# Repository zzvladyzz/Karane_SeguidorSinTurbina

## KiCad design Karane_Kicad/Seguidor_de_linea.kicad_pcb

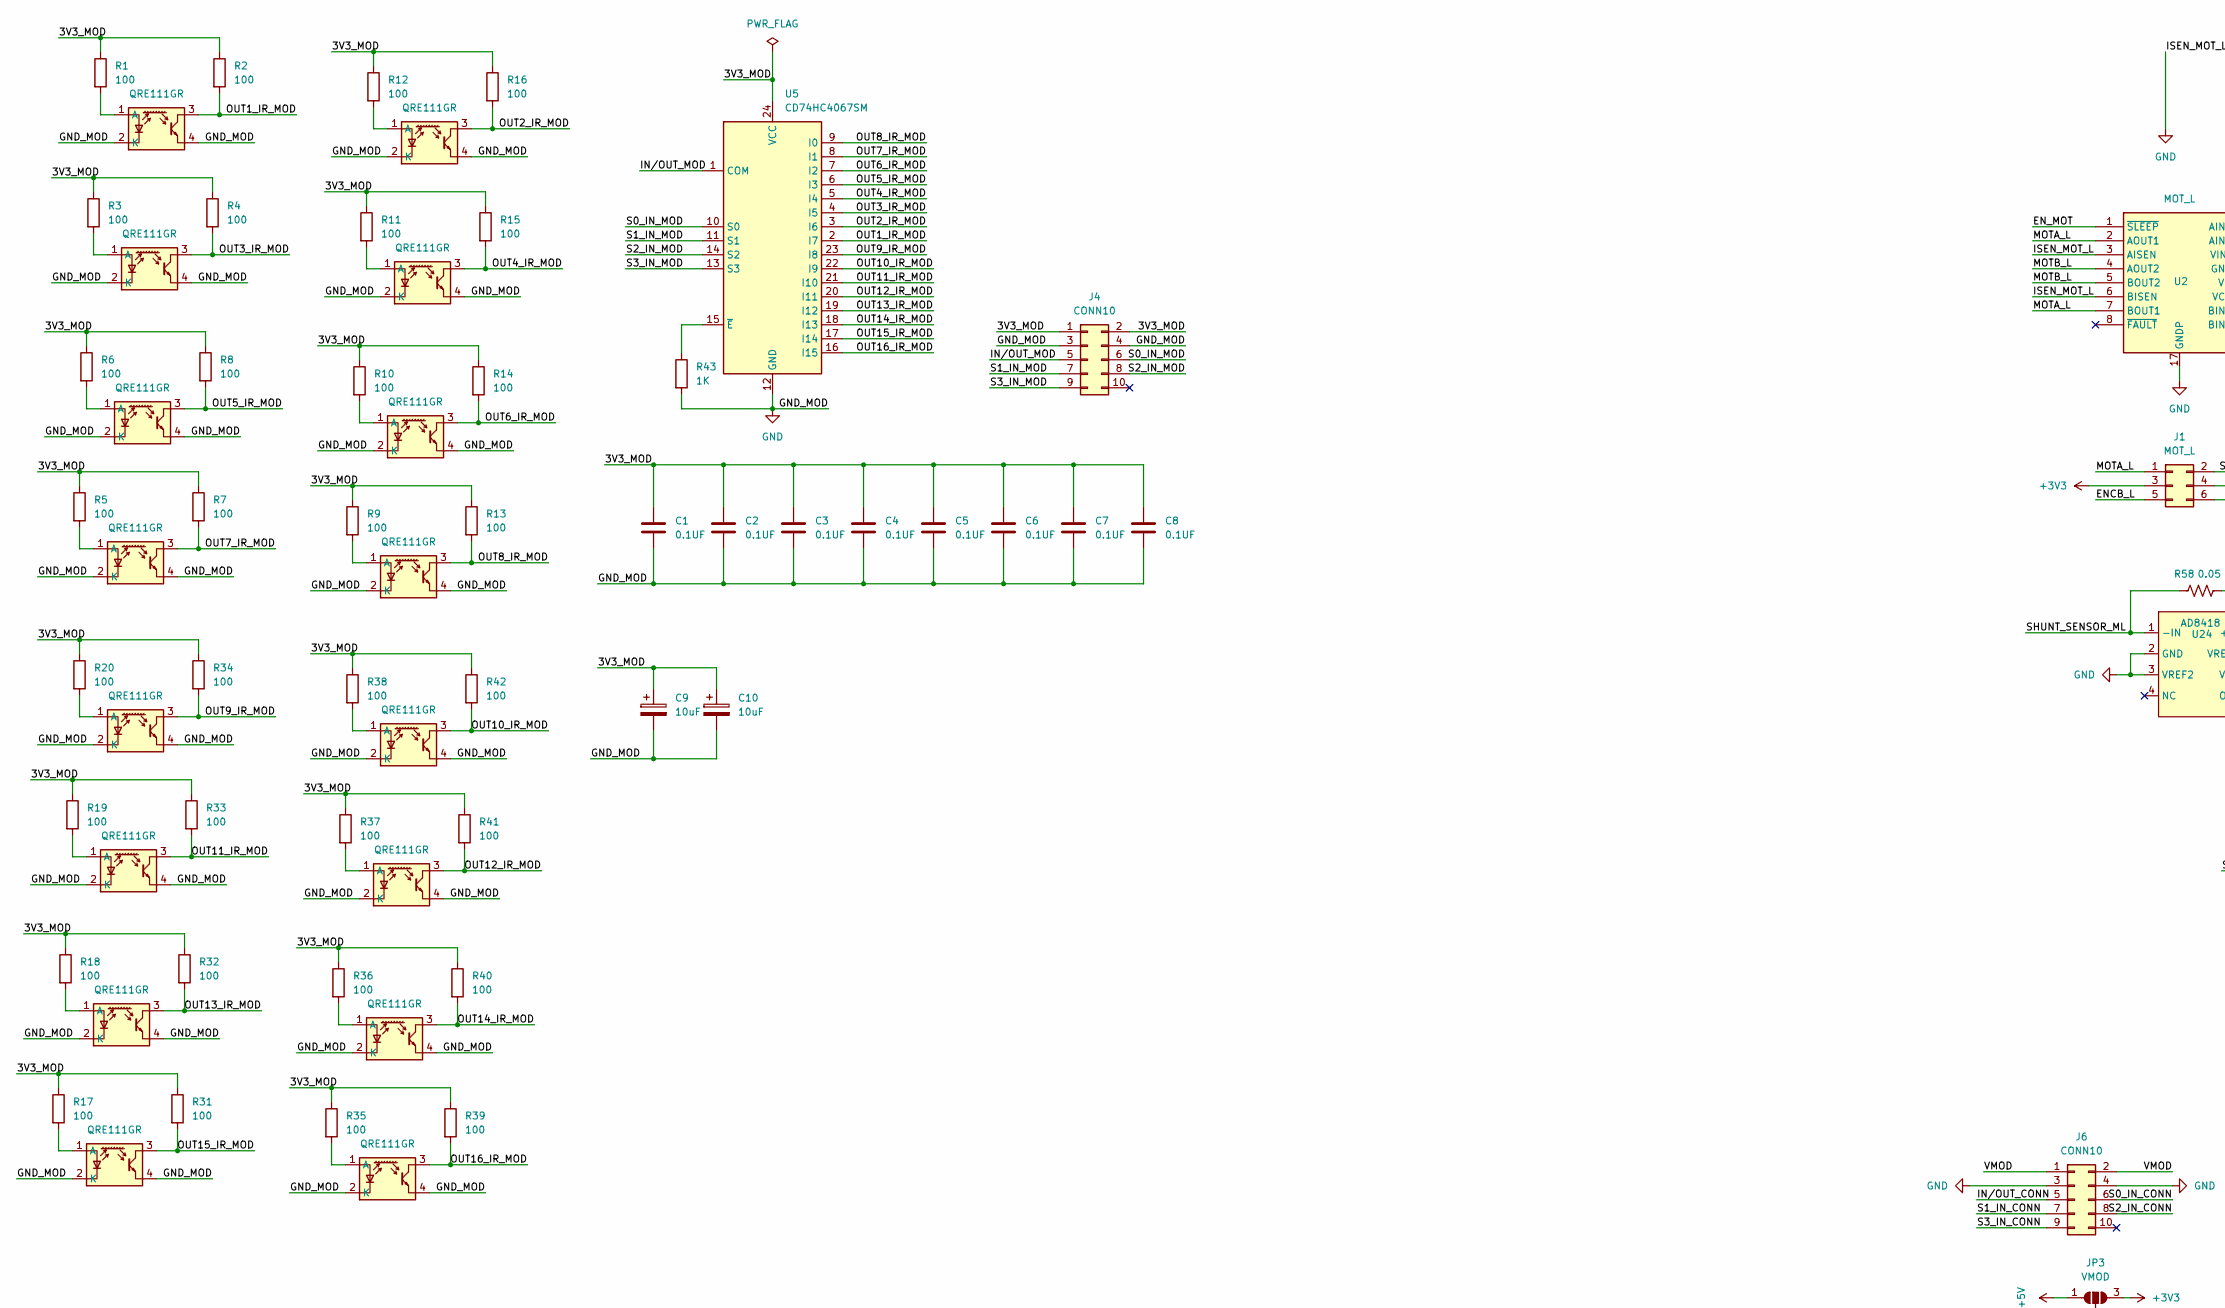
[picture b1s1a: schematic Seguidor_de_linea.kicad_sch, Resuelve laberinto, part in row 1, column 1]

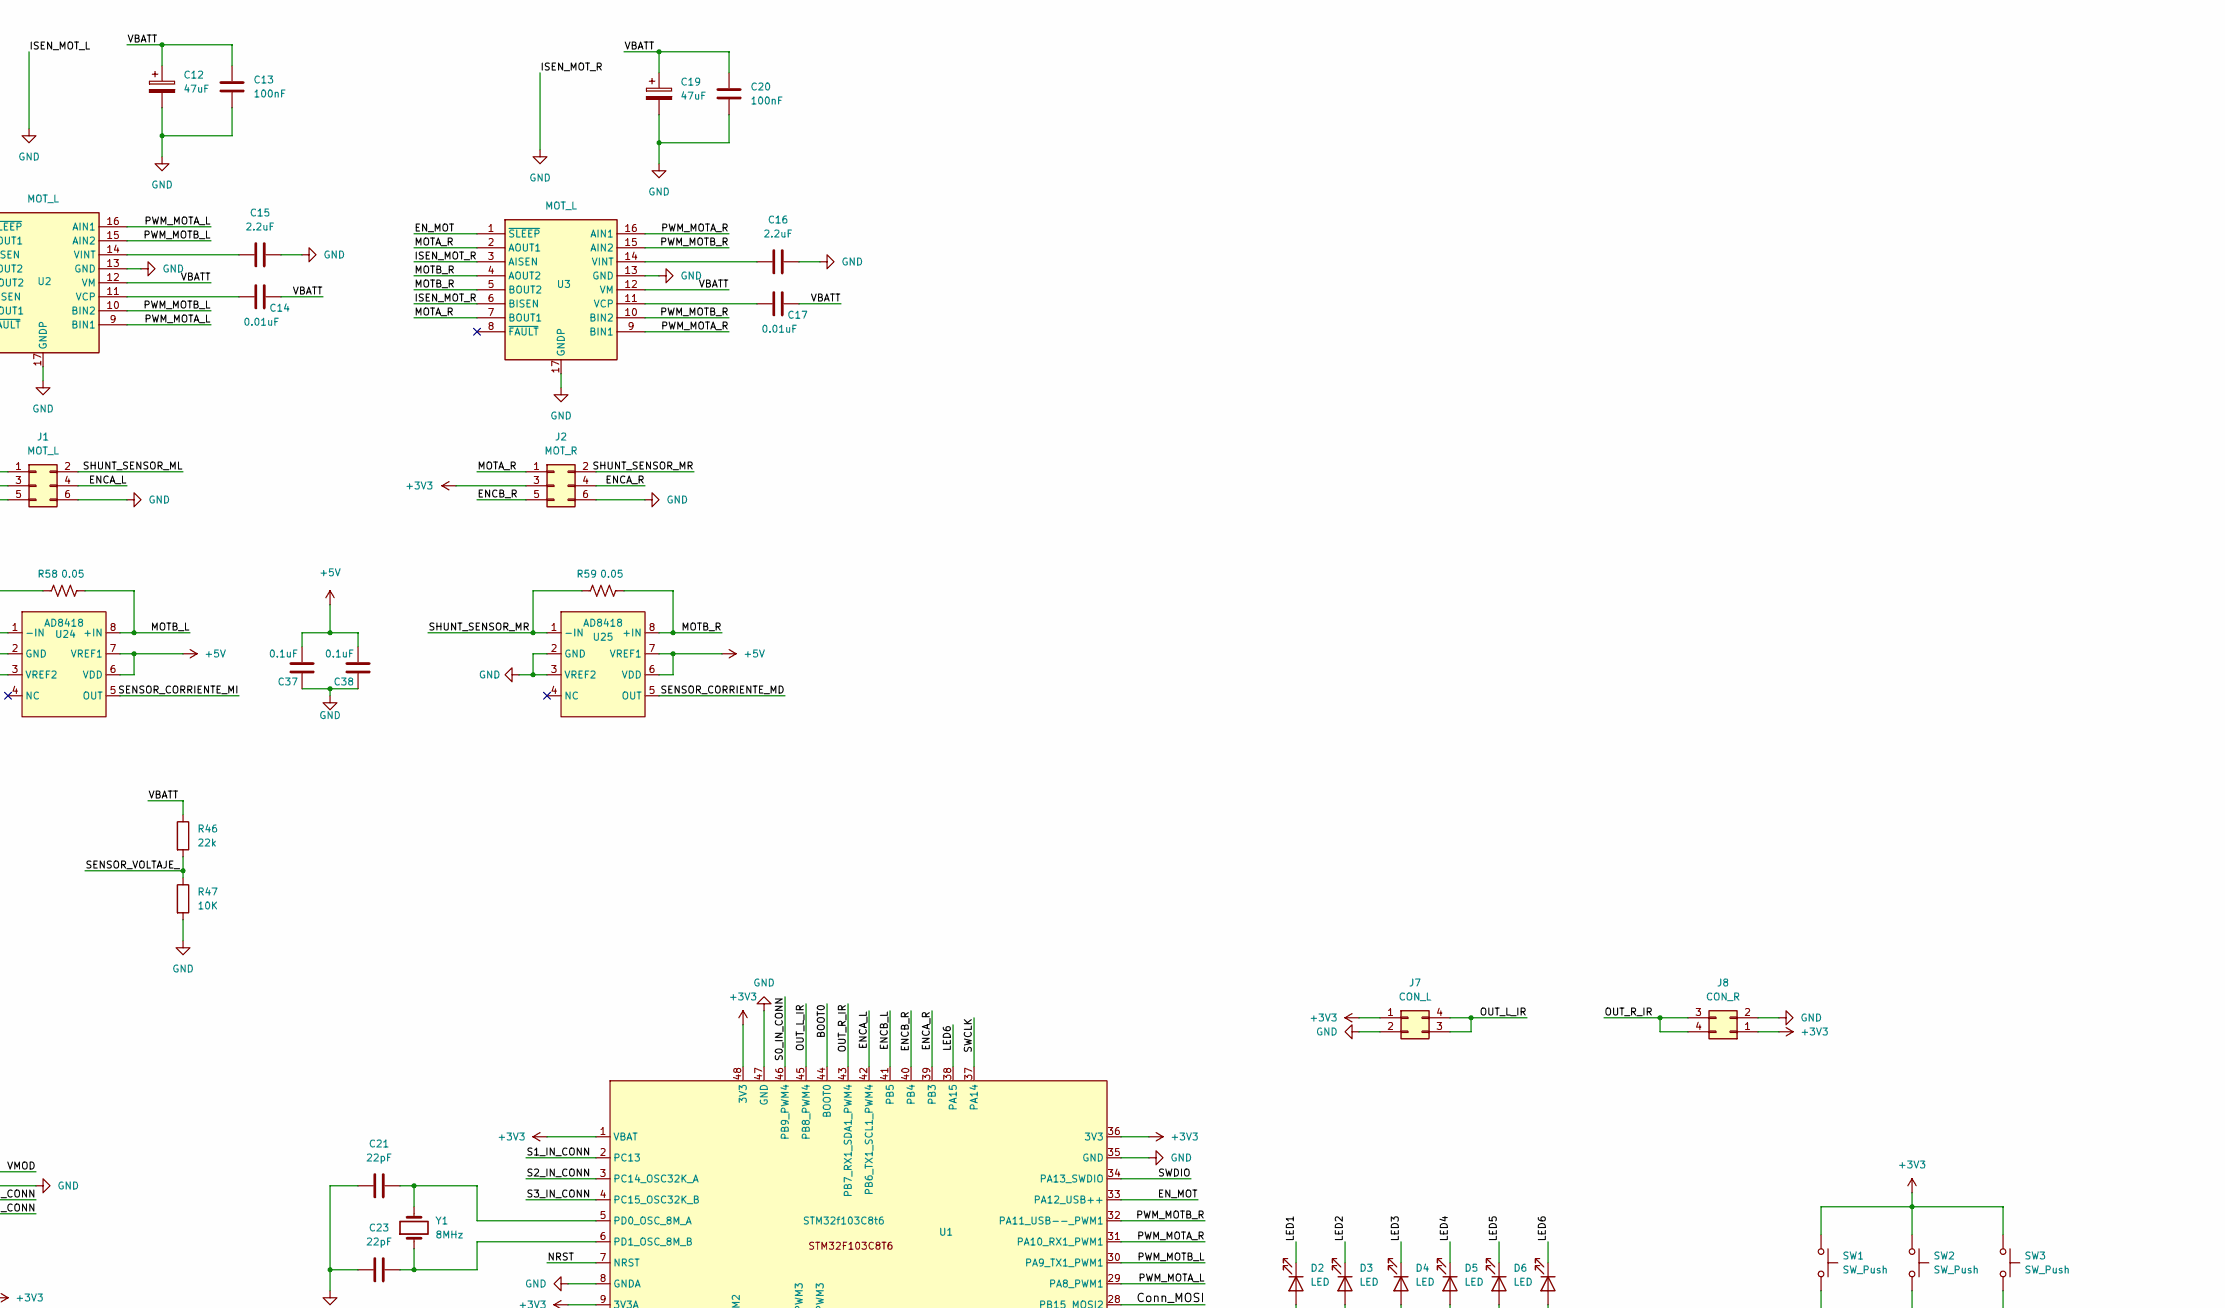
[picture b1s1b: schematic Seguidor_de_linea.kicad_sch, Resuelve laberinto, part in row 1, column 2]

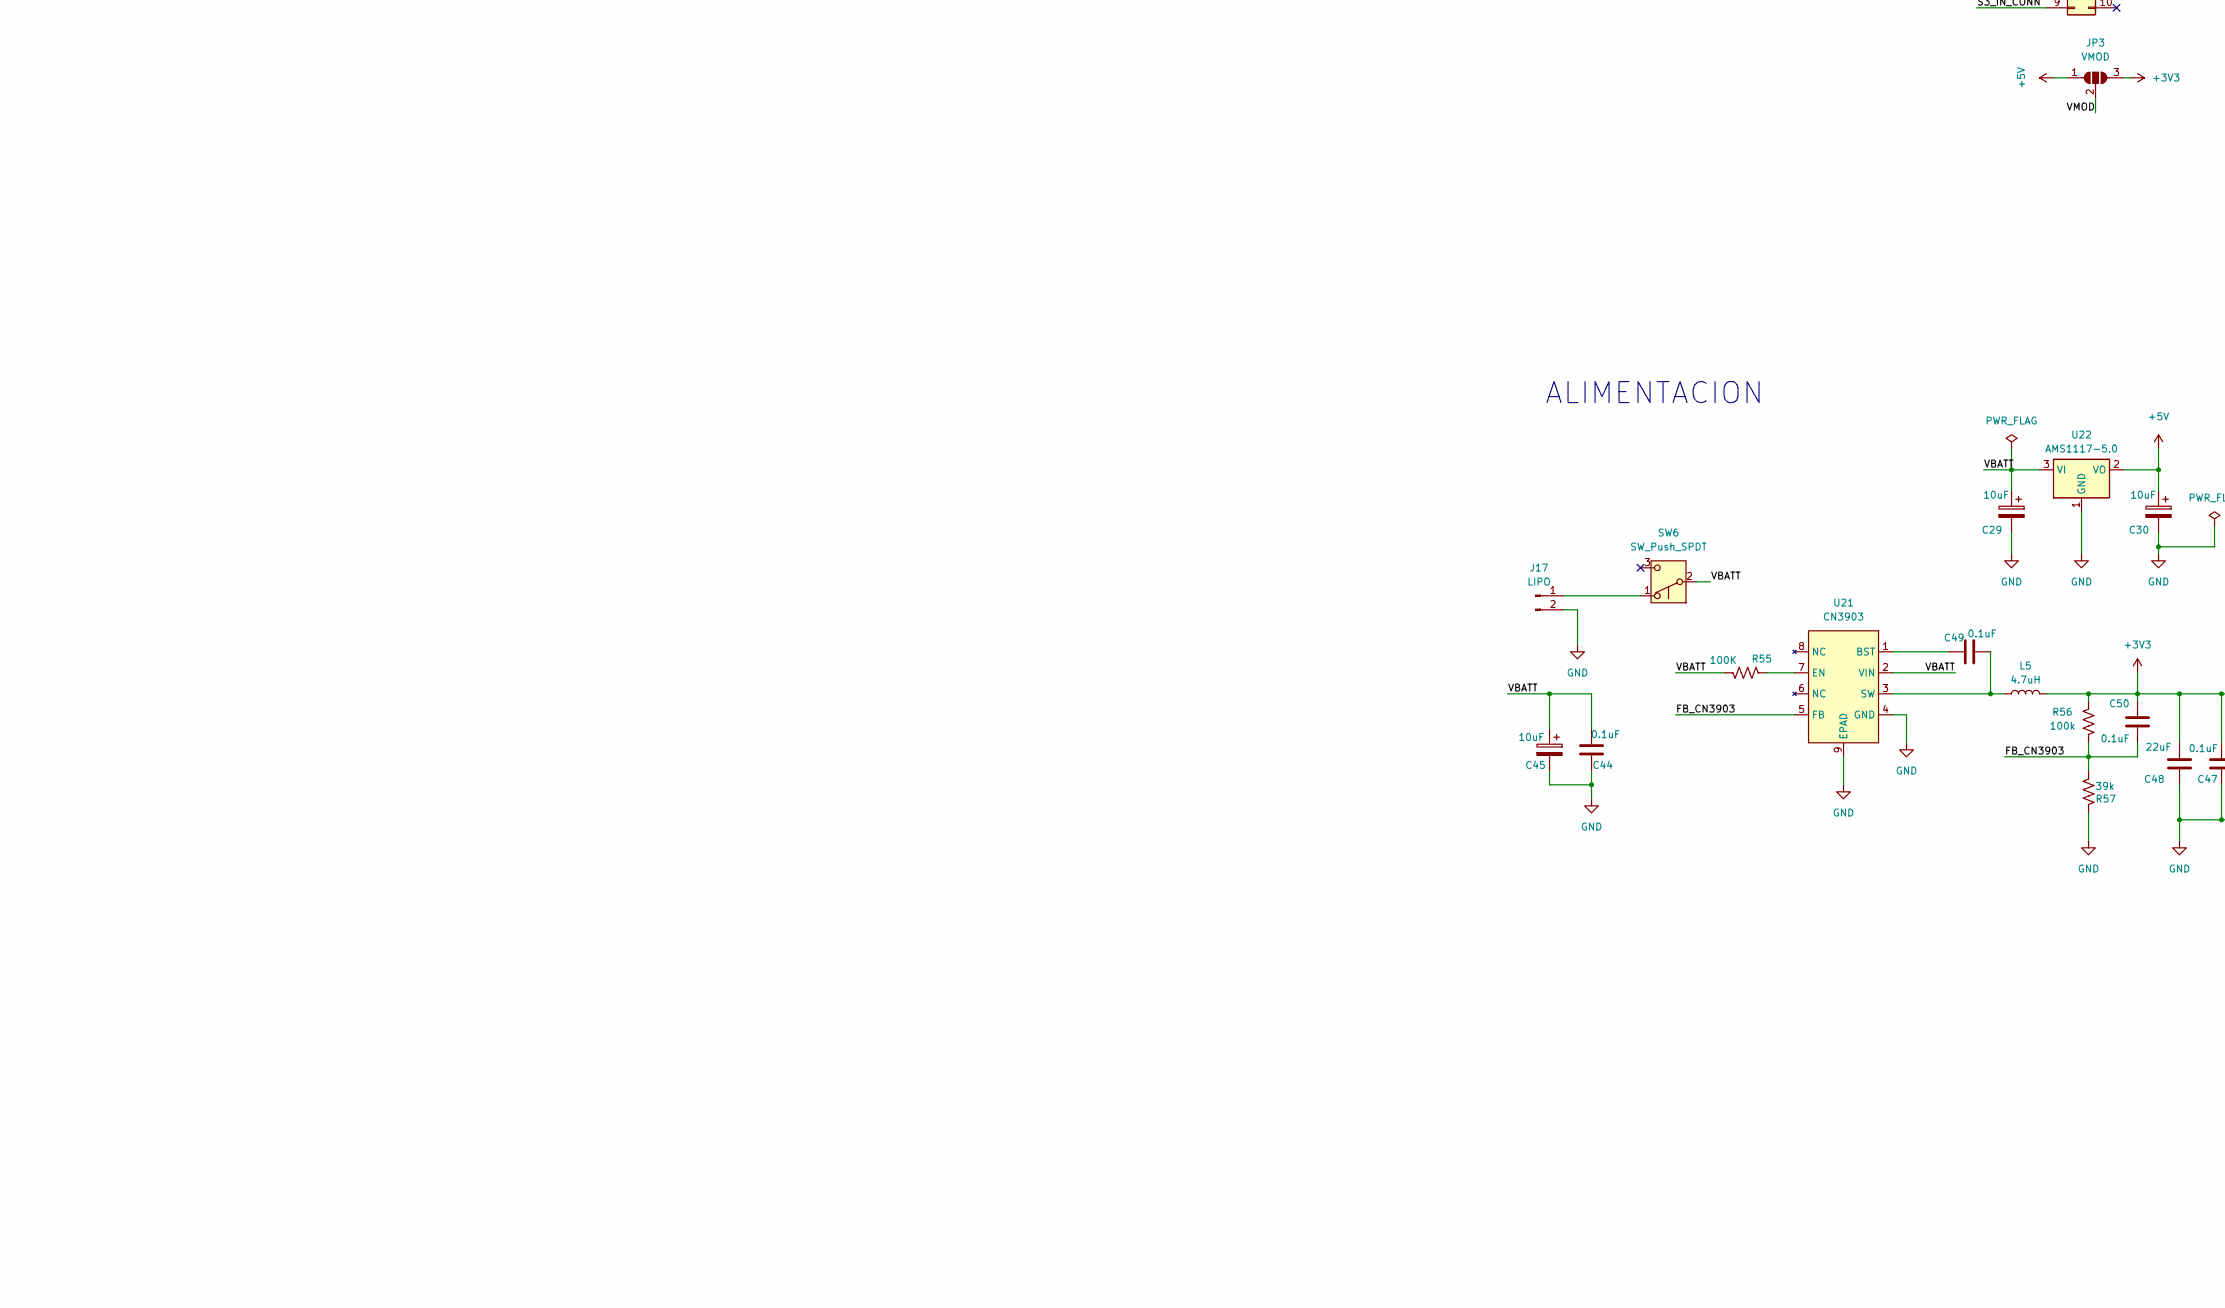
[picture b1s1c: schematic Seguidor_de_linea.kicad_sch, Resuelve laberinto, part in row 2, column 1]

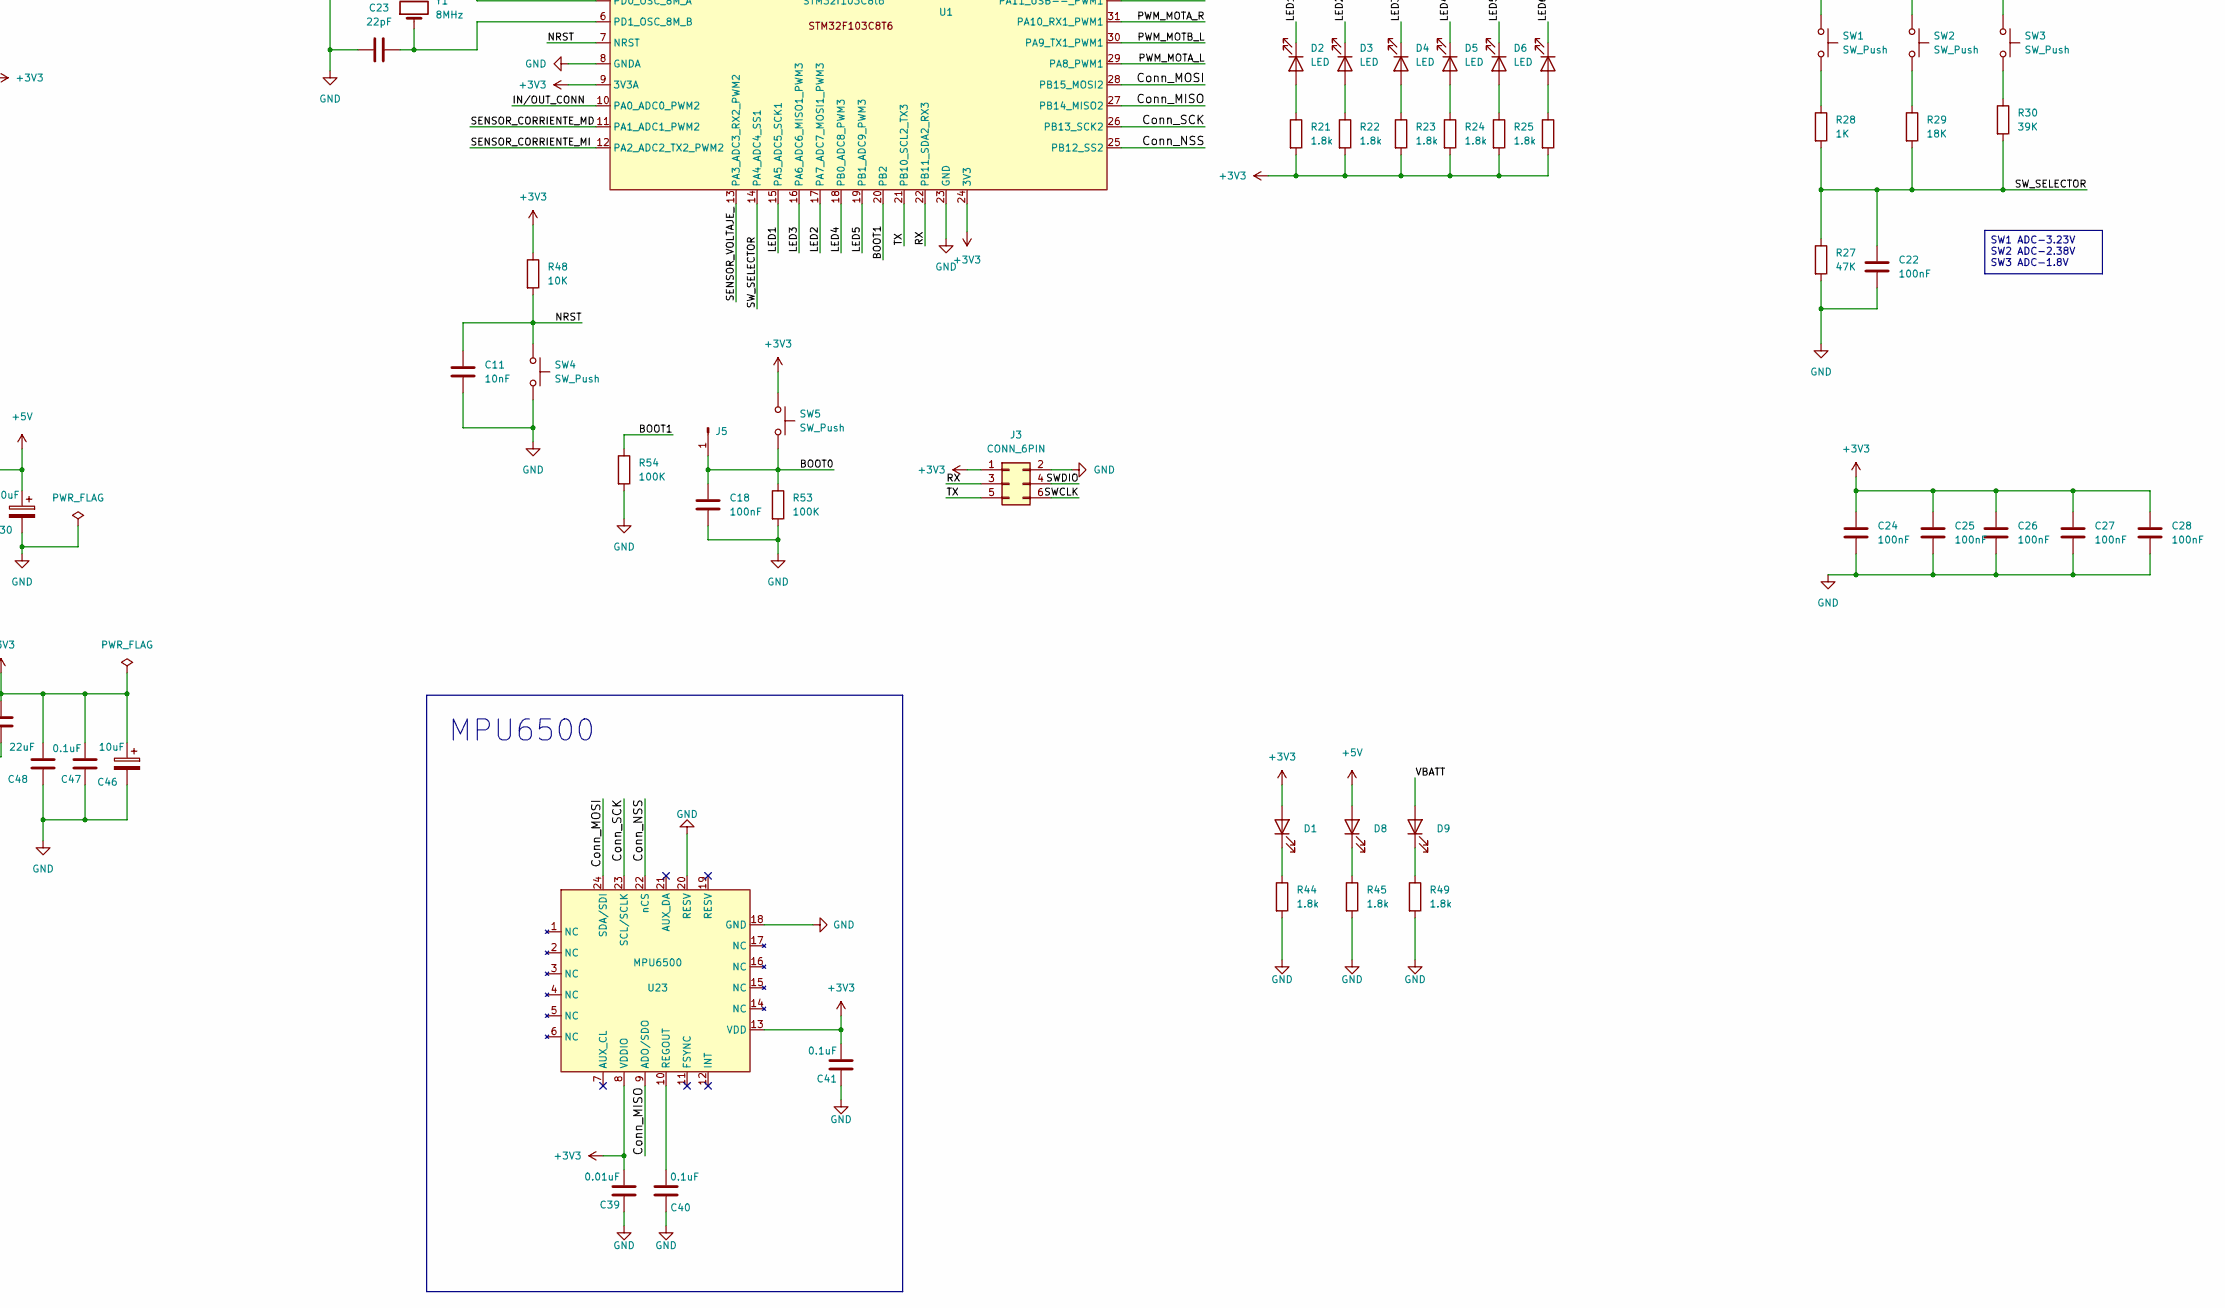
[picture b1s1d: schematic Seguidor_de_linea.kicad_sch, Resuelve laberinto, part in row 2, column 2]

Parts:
C1, C2, C3, C4, C5, C6, C7, C8: 0.1UF; C_1206_3216Metric_Pad1.33x1.80mm_HandSolder
C9, C10: 10uF; CP_EIA-6032-15_Kemet-U_HandSolder
C11: 10nF; C_1206_3216Metric_Pad1.33x1.80mm_HandSolder
C12, C19: 47uF; C_1210_3225Metric_Pad1.33x2.70mm_HandSolder
C13, C18, C20, C22, C24, C25, C26, C27, C28: 100nF; C_1206_3216Metric_Pad1.33x1.80mm_HandSolder
C14, C17: 0.01uF; C_1206_3216Metric_Pad1.33x1.80mm_HandSolder
C15, C16: 2.2uF; C_1206_3216Metric_Pad1.33x1.80mm_HandSolder
C21, C23: 22pF; C_0805_2012Metric_Pad1.18x1.45mm_HandSolder
C29, C45, C46: 10uF; CP_Elec_4x5.4
C30: 10uF; C_1206_3216Metric_Pad1.33x1.80mm_HandSolder
C37, C38, C44, C47, C49, C50: 0.1uF; C_1206_3216Metric_Pad1.33x1.80mm_HandSolder
C39: 0.01uF; C_0805_2012Metric_Pad1.18x1.45mm_HandSolder
C40, C41: 0.1uF; C_0805_2012Metric_Pad1.18x1.45mm_HandSolder
C48: 22uF; C_1206_3216Metric_Pad1.33x1.80mm_HandSolder
D1, D2, D3, D4, D5, D6, D7, D8, D9: LED; LED_1206_3216Metric
J1: MOT_L; IDC-Header_2x03_P2.54mm_Vertical
J2: MOT_R; IDC-Header_2x03_P2.54mm_Vertical
J3: CONN_6PIN; IDC-Header_2x03_P2.54mm_Vertical
J4, J6: CONN10; IDC-Header_2x05_P2.54mm_Vertical
J5: NRST; PinHeader_1x01_P2.54mm_Vertical
J7: CON_L; PinHeader_2x02_P2.54mm_Vertical
J8: CON_R; PinHeader_2x02_P2.54mm_Vertical
J17: LIPO; PinHeader_1x02_P2.54mm_Vertical
JP3: VMOD; SolderJumper-3_P1.3mm_Open_Pad1.0x1.5mm_NumberLabels
L5: 4.7uH; L_Wuerth_HCM-7050
R1, R2, R3, R4, R5, R6, R7, R8, R9, R10, R11, R12, R13, R14, R15, R16, R17, R18, R19, R20, R31, R32, R33, R34, R35, R36, R37, R38, R39, R40, R41, R42: 100; R_1206_3216Metric_Pad1.30x1.75mm_HandSolder
R21, R22, R23, R24, R25, R26, R44, R45, R49: 1.8k; R_1206_3216Metric
R27: 47K; R_1206_3216Metric
R28, R43: 1K; R_1206_3216Metric
R29: 18K; R_1206_3216Metric
R30: 39K; R_1206_3216Metric
R46: 22k; R_1206_3216Metric
R47, R48: 10K; R_1206_3216Metric
R53, R54: 100K; R_1206_3216Metric
R55: 100K; R_0805_2012Metric_Pad1.20x1.40mm_HandSolder
R56: 100k; R_0805_2012Metric_Pad1.20x1.40mm_HandSolder
R57: 39k; R_0805_2012Metric_Pad1.20x1.40mm_HandSolder
R58, R59: 0.05; R_2512_6332Metric_Pad1.40x3.35mm_HandSolder
SW1, SW2, SW3, SW4, SW5: SW_Push; SW_SPST_CK_RS282G05A3
SW6: SW_Push_SPDT; SW_SPDT_PCM12
U1: STM32f103C8t6; LQFP-48_7x7mm_P0.5mm
U2, U3: MOT_L; HTSSOP-16-1EP_4.4x5mm_P0.65mm_EP3.4x5mm_Mask2.46x2.31mm_The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
U4, U6, U7, U8, U9, U10, U11, U12, U13, U14, U15, U16, U17, U18, U19, U20: QRE111GR; QRE1113GR_IR
U5: CD74HC4067SM; SSOP-24_5.3x8.2mm_P0.65mm
U21: CN3903; SOP-8-1EP_4.57x4.57mm_P1.27mm_EP4.57x4.45mm
U22: AMS1117-5.0; SOT-223-3_TabPin2
U23: MPU6500; InvenSense_QFN-24_3x3mm_P0.4mm
U24, U25: AD8418
Y1: 8MHz; Crystal_HC49-U_Vertical

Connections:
+3V3: C24.1, C25.1, C26.1, C27.1, C28.1, C39.2, C41.2, C46.1, C47.1, C48.1, C50.2, D1.2 (A), J1.3, J2.3, J3.1, J7.1, J8.1, JP3.3 (B), L5.1, R21.2, R22.2, R23.2, R24.2, R25.2, R26.2, R48.1, R56.1, SW1.1, SW2.1, SW3.1, SW5.1, U1.1 (VBAT), U1.9 (3V3A), U1.24 (3V3), U1.36 (3V3), U1.48 (3V3), U23.8 (VDDIO), U23.13 (VDD)
+5V: C30.1, C37.2, C38.2, D8.2 (A), JP3.1 (A), U22.2 (VO), U24.6 (VDD), U24.7 (VREF1), U25.6 (VDD), U25.7 (VREF1)
/3V3_MOD: C1.1, C2.1, C3.1, C4.1, C5.1, C6.1, C7.1, C8.1, C9.1, C10.1, J4.1, J4.2, R1.1, R2.1, R3.1, R4.1, R5.1, R6.1, R7.1, R8.1, R9.1, R10.1, R11.1, R12.1, R13.1, R14.1, R15.1, R16.1, R17.1, R18.1, R19.1, R20.1, R31.1, R32.1, R33.1, R34.1, R35.1, R36.1, R37.1, R38.1, R39.1, R40.1, R41.1, R42.1, U5.24 (VCC)
/BOOT0: C18.1, J5.1, R53.1, SW5.2, U1.44 (BOOT0)
/BOOT1: R54.1, U1.20 (PB2)
/Conn_MISO: U1.27 (PB14_MISO2), U23.9 (ADO/SDO)
/Conn_MOSI: U1.28 (PB15_MOSI2), U23.24 (SDA/SDI)
/Conn_NSS: U1.25 (PB12_SS2), U23.22 (nCS)
/Conn_SCK: U1.26 (PB13_SCK2), U23.23 (SCL/SCLK)
/ENCA_L: J1.4, U1.42 (PB6_TX1_SCL1_PWM4)
/ENCA_R: J2.4, U1.39 (PB3)
/ENCB_L: J1.5, U1.41 (PB5)
/ENCB_R: J2.5, U1.40 (PB4)
/EN_MOT: U1.33 (PA12_USB++), U2.1 (~SLEEP), U3.1 (~SLEEP)
/FB_CN3903: C50.1, R56.2, R57.1, U21.5 (FB)
/IN/OUT_CONN: J6.5, U1.10 (PA0_ADC0_PWM2)
/IN/OUT_MOD: J4.5, U5.1 (COM)
/LED1: D2.1 (K), U1.15 (PA5_ADC5_SCK1)
/LED2: D3.1 (K), U1.17 (PA7_ADC7_MOSI1_PWM3)
/LED3: D4.1 (K), U1.16 (PA6_ADC6_MISO1_PWM3)
/LED4: D5.1 (K), U1.18 (PB0_ADC8_PWM3)
/LED5: D6.1 (K), U1.19 (PB1_ADC9_PWM3)
/LED6: D7.1 (K), U1.38 (PA15)
/MOTA_L: J1.1, U2.2 (AOUT1), U2.7 (BOUT1)
/MOTA_R: J2.1, U3.2 (AOUT1), U3.7 (BOUT1)
/MOTB_L: R58.2, U2.4 (AOUT2), U2.5 (BOUT2), U24.8 (+IN)
/MOTB_R: R59.2, U3.4 (AOUT2), U3.5 (BOUT2), U25.8 (+IN)
/NRST: C11.1, R48.2, SW4.1, U1.7 (NRST)
/OUT1_IR_MOD: R2.2, U4.3, U5.2 (I7)
/OUT2_IR_MOD: R16.2, U5.3 (I6), U12.3
/OUT3_IR_MOD: R4.2, U5.4 (I5), U6.3
/OUT4_IR_MOD: R15.2, U5.5 (I4), U11.3
/OUT5_IR_MOD: R8.2, U5.6 (I3), U8.3
/OUT6_IR_MOD: R14.2, U5.7 (I2), U10.3
/OUT7_IR_MOD: R7.2, U5.8 (I1), U7.3
/OUT8_IR_MOD: R13.2, U5.9 (I0), U9.3
/OUT9_IR_MOD: R34.2, U5.23 (I8), U16.3
/OUT10_IR_MOD: R42.2, U5.22 (I9), U20.3
/OUT11_IR_MOD: R33.2, U5.21 (I10), U15.3
/OUT12_IR_MOD: R41.2, U5.20 (I11), U19.3
/OUT13_IR_MOD: R32.2, U5.19 (I12), U14.3
/OUT14_IR_MOD: R40.2, U5.18 (I13), U18.3
/OUT15_IR_MOD: R31.2, U5.17 (I14), U13.3
/OUT16_IR_MOD: R39.2, U5.16 (I15), U17.3
/OUT_L_IR: J7.3, J7.4, U1.45 (PB8_PWM4)
/OUT_R_IR: J8.3, J8.4, U1.43 (PB7_RX1_SDA1_PWM4)
/PWM_MOTA_L: U1.29 (PA8_PWM1), U2.9 (BIN1), U2.16 (AIN1)
/PWM_MOTA_R: U1.31 (PA10_RX1_PWM1), U3.9 (BIN1), U3.16 (AIN1)
/PWM_MOTB_L: U1.30 (PA9_TX1_PWM1), U2.10 (BIN2), U2.15 (AIN2)
/PWM_MOTB_R: U1.32 (PA11_USB--_PWM1), U3.10 (BIN2), U3.15 (AIN2)
/RX: J3.3, U1.22 (PB11_SDA2_RX3)
/S0_IN_CONN: J6.6, U1.46 (PB9_PWM4)
/S0_IN_MOD: J4.6, U5.10 (S0)
/S1_IN_CONN: J6.7, U1.2 (PC13)
/S1_IN_MOD: J4.7, U5.11 (S1)
/S2_IN_CONN: J6.8, U1.3 (PC14_OSC32K_A)
/S2_IN_MOD: J4.8, U5.14 (S2)
/S3_IN_CONN: J6.9, U1.4 (PC15_OSC32K_B)
/S3_IN_MOD: J4.9, U5.13 (S3)
/SENSOR_CORRIENTE_MD: U1.11 (PA1_ADC1_PWM2), U25.5 (OUT)
/SENSOR_CORRIENTE_MI: U1.12 (PA2_ADC2_TX2_PWM2), U24.5 (OUT)
/SENSOR_VOLTAJE_: R46.2, R47.1, U1.13 (PA3_ADC3_RX2_PWM2)
/SHUNT_SENSOR_ML: J1.2, R58.1, U24.1 (-IN)
/SHUNT_SENSOR_MR: J2.2, R59.1, U25.1 (-IN)
/SWCLK: J3.6, U1.37 (PA14)
/SWDIO: J3.4, U1.34 (PA13_SWDIO)
/SW_SELECTOR: C22.1, R27.1, R28.2, R29.2, R30.2, U1.14 (PA4_ADC4_SS1)
/TX: J3.5, U1.21 (PB10_SCL2_TX3)
/VBATT: C12.1, C13.1, C14.2, C17.2, C19.1, C20.1, C29.1, C44.1, C45.1, D9.2 (A), R46.1, R55.2, SW6.2 (B), U2.12 (VM), U3.12 (VM), U21.2 (VIN), U22.3 (VI)
/VMOD: J6.1, J6.2, JP3.2 (C)
GND: C1.2, C2.2, C3.2, C4.2, C5.2, C6.2, C7.2, C8.2, C9.2, C10.2, C11.2, C12.2, C13.2, C15.2, C16.2, C18.2, C19.2, C20.2, C21.1, C22.2, C23.2, C24.2, C25.2, C26.2, C27.2, C28.2, C29.2, C30.2, C37.1, C38.1, C39.1, C40.1, C41.1, C44.2, C45.2, C46.2, C47.2, C48.2, J1.6, J2.6, J3.2, J4.3, J4.4, J6.3, J6.4, J7.2, J8.2, J17.2, R27.2, R43.2, R44.2, R45.2, R47.2, R49.2, R53.2, R54.2, R57.2, SW4.2, U1.8 (GNDA), U1.23 (GND), U1.35 (GND), U1.47 (GND), U2.3 (AISEN), U2.6 (BISEN), U2.13 (GND), U2.17 (GNDP), U3.3 (AISEN), U3.6 (BISEN), U3.13 (GND), U3.17 (GNDP), U4.2 (K), U4.4, U5.12 (GND), U6.2 (K), U6.4, U7.2 (K), U7.4, U8.2 (K), U8.4, U9.2 (K), U9.4, U10.2 (K), U10.4, U11.2 (K), U11.4, U12.2 (K), U12.4, U13.2 (K), U13.4, U14.2 (K), U14.4, U15.2 (K), U15.4, U16.2 (K), U16.4, U17.2 (K), U17.4, U18.2 (K), U18.4, U19.2 (K), U19.4, U20.2 (K), U20.4, U21.4 (GND), U21.9 (EPAD), U22.1 (GND), U23.18 (GND), U23.20 (RESV), U24.2 (GND), U24.3 (VREF2), U25.2 (GND), U25.3 (VREF2)
unnamed: D1.1 (K), R44.1
unnamed: D2.2 (A), R21.1
unnamed: D3.2 (A), R22.1
unnamed: D4.2 (A), R23.1
unnamed: D5.2 (A), R24.1
unnamed: D6.2 (A), R25.1
unnamed: D7.2 (A), R26.1
unnamed: D8.1 (K), R45.1
unnamed: D9.1 (K), R49.1
unnamed: J17.1, SW6.1 (A)
unnamed: R28.1, SW1.2
unnamed: R29.1, SW2.2
unnamed: R30.1, SW3.2
unnamed: C21.2, U1.5 (PD0_OSC_8M_A), Y1.2
unnamed: C23.1, U1.6 (PD1_OSC_8M_B), Y1.1
unnamed: C14.1, U2.11 (VCP)
unnamed: C15.1, U2.14 (VINT)
unnamed: C17.1, U3.11 (VCP)
unnamed: C16.1, U3.14 (VINT)
unnamed: R1.2, U4.1 (A)
unnamed: R43.1, U5.15 (~E)
unnamed: R3.2, U6.1 (A)
unnamed: R5.2, U7.1 (A)
unnamed: R6.2, U8.1 (A)
unnamed: R9.2, U9.1 (A)
unnamed: R10.2, U10.1 (A)
unnamed: R11.2, U11.1 (A)
unnamed: R12.2, U12.1 (A)
unnamed: R17.2, U13.1 (A)
unnamed: R18.2, U14.1 (A)
unnamed: R19.2, U15.1 (A)
unnamed: R20.2, U16.1 (A)
unnamed: R35.2, U17.1 (A)
unnamed: R36.2, U18.1 (A)
unnamed: R37.2, U19.1 (A)
unnamed: R38.2, U20.1 (A)
unnamed: C49.2, U21.1 (BST)
unnamed: R55.1, U21.7 (EN)
unnamed: C49.1, L5.2, U21.3 (SW)
unnamed: C40.2, U23.10 (REGOUT)

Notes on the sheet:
MPU6500
ALIMENTACION
SW1 ADC-3.23V SW2 ADC-2.38V SW3 ADC-1.8V

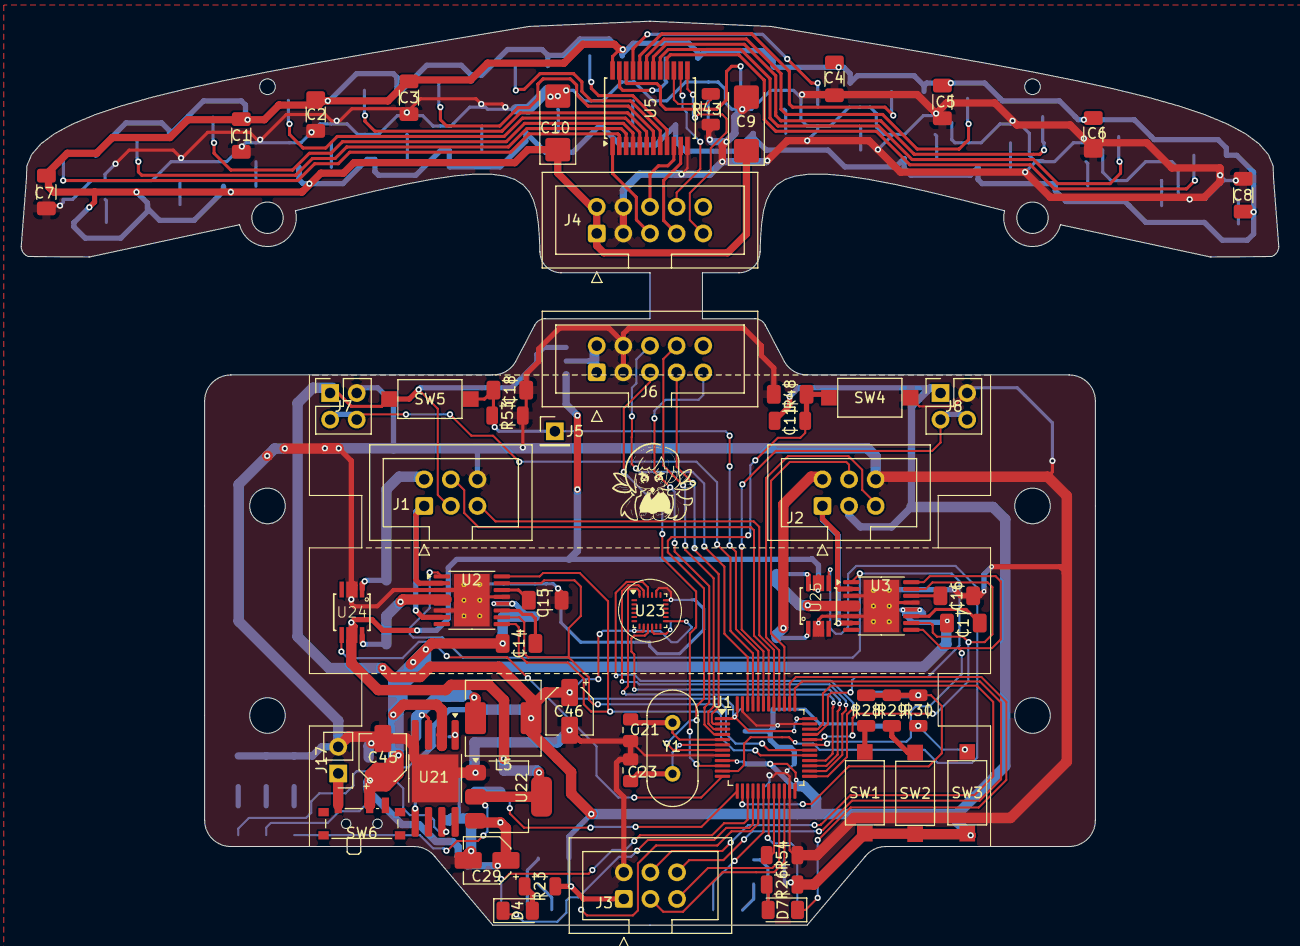
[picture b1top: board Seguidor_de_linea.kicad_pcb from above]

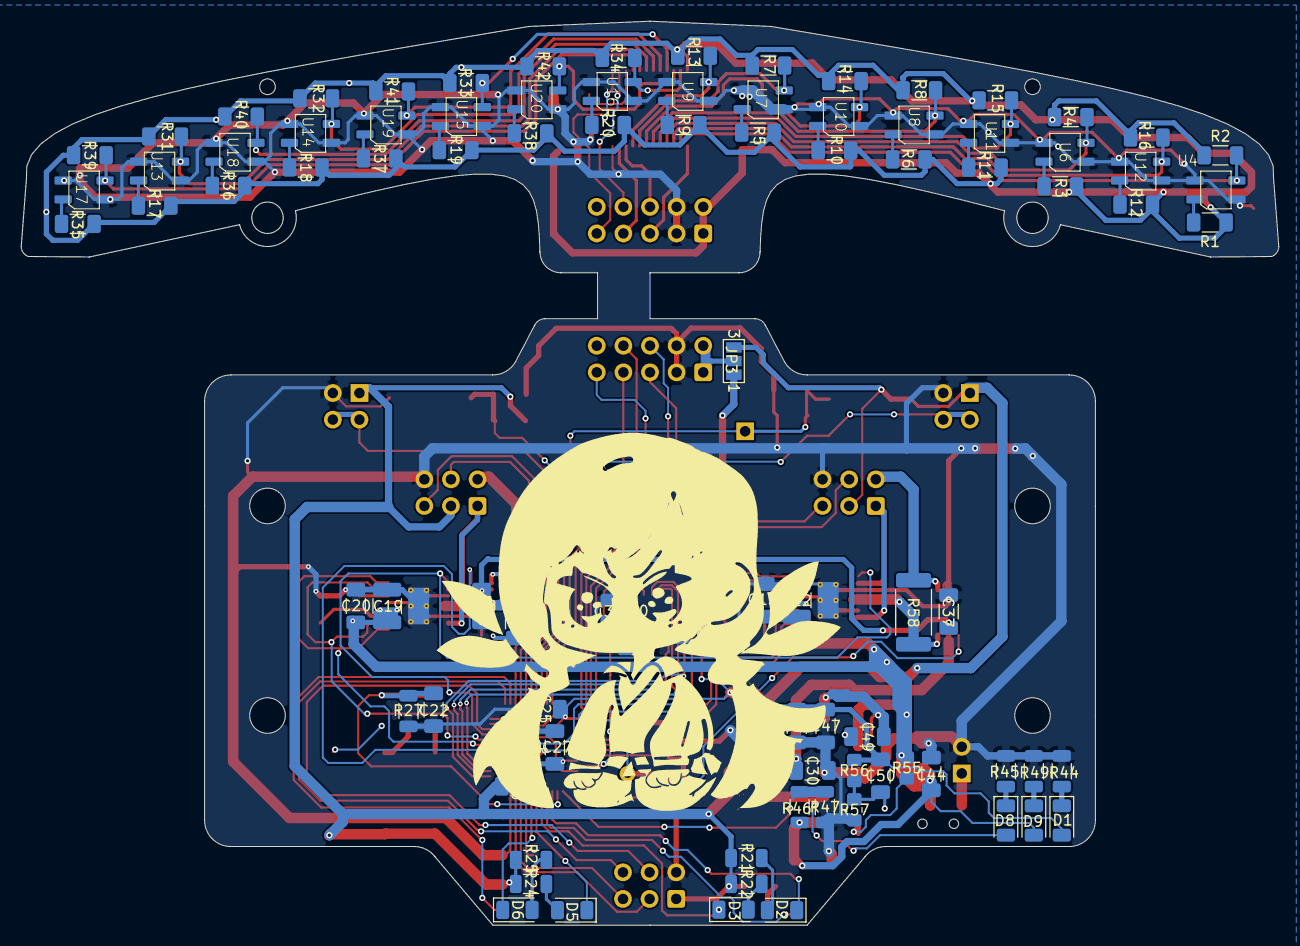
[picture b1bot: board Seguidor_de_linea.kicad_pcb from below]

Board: 2 copper layers, 120.0 x 86.3 mm, 152 parts (93 on the bottom side), 111 nets.

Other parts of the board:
., .#2: LOGO

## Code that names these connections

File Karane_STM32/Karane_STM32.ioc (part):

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Mcu.Name=STM32F103C(8-B)Tx
Mcu.Package=LQFP48
Mcu.UserName=STM32F103C8Tx
PA0-WKUP.GPIOParameters=GPIO_Label
PA0-WKUP.GPIO_Label=IN_mux
PA0-WKUP.Signal=ADCx_IN0
PA1.GPIOParameters=GPIO_Label
PA1.GPIO_Label=SensorAmp_MD
PA1.Signal=ADCx_IN1
PA10.GPIOParameters=GPIO_Label
PA10.GPIO_Label=PWM_MOTA_R
PA10.Signal=S_TIM1_CH3
PA11.GPIOParameters=GPIO_Label
PA11.GPIO_Label=PWM_MOTB_R
PA11.Signal=S_TIM1_CH4
PA12.GPIOParameters=GPIO_Label
PA12.GPIO_Label=EN_MOT
PA12.Signal=GPIO_Output
PA13.Mode=Serial_Wire
PA13.Signal=SYS_JTMS-SWDIO
PA14.Mode=Serial_Wire
PA14.Signal=SYS_JTCK-SWCLK
PA15.GPIOParameters=PinState,GPIO_Label
PA15.GPIO_Label=LED6
PA15.PinState=GPIO_PIN_SET
PA15.Signal=GPIO_Output
PA2.GPIOParameters=GPIO_Label
PA2.GPIO_Label=SensorAmp_MI
PA2.Signal=ADCx_IN2
PA3.GPIOParameters=GPIO_Label
PA3.GPIO_Label=Sensor_Voltaje
PA3.Signal=ADCx_IN3
PA4.GPIOParameters=GPIO_Label
PA4.GPIO_Label=SW_Selector
PA4.Signal=ADCx_IN4
PA5.GPIOParameters=PinState,GPIO_Label
PA5.GPIO_Label=LED1
PA5.PinState=GPIO_PIN_SET
PA5.Signal=GPIO_Output
PA6.GPIOParameters=PinState,GPIO_Label
PA6.GPIO_Label=LED3
PA6.PinState=GPIO_PIN_SET
PA6.Signal=GPIO_Output
PA7.GPIOParameters=PinState,GPIO_Label
PA7.GPIO_Label=LED2
PA7.PinState=GPIO_PIN_SET
PA7.Signal=GPIO_Output
PA8.GPIOParameters=GPIO_Label
PA8.GPIO_Label=PWM_MOTA_L
PA8.Signal=S_TIM1_CH1
PA9.GPIOParameters=GPIO_Label
PA9.GPIO_Label=PWM_MOTB_L
PA9.Signal=S_TIM1_CH2
PB0.GPIOParameters=PinState,GPIO_Label
PB0.GPIO_Label=LED4
PB0.PinState=GPIO_PIN_SET
PB0.Signal=GPIO_Output
PB1.GPIOParameters=PinState,GPIO_Label
PB1.GPIO_Label=LED5
PB1.PinState=GPIO_PIN_SET
PB1.Signal=GPIO_Output
PB10.Mode=Asynchronous
PB10.Signal=USART3_TX
PB11.Mode=Asynchronous
PB11.Signal=USART3_RX
PB12.GPIOParameters=GPIO_Speed,PinState,GPIO_Label
PB12.GPIO_Label=SPI_NSS
PB12.GPIO_Speed=GPIO_SPEED_FREQ_HIGH
PB12.PinState=GPIO_PIN_SET
PB12.Signal=GPIO_Output
PB13.Mode=Full_Duplex_Master
PB13.Signal=SPI2_SCK
PB14.Mode=Full_Duplex_Master
PB14.Signal=SPI2_MISO
PB15.Mode=Full_Duplex_Master
PB15.Signal=SPI2_MOSI
PB2.GPIOParameters=GPIO_Label
PB2.GPIO_Label=BOOT1
PB2.Signal=GPIO_Output
PB3.GPIOParameters=GPIO_Label,GPIO_ModeDefaultEXTI
PB3.GPIO_Label=ENCA_R
PB3.GPIO_ModeDefaultEXTI=GPIO_MODE_IT_RISING_FALLING
PB3.Signal=GPXTI3
PB4.GPIOParameters=GPIO_Label,GPIO_ModeDefaultEXTI
PB4.GPIO_Label=ENCB_R
PB4.GPIO_ModeDefaultEXTI=GPIO_MODE_IT_RISING_FALLING
PB4.Signal=GPXTI4
PB5.GPIOParameters=GPIO_Label,GPIO_ModeDefaultEXTI
PB5.GPIO_Label=ENCB_L
PB5.GPIO_ModeDefaultEXTI=GPIO_MODE_IT_RISING_FALLING
PB5.Signal=GPXTI5
PB6.GPIOParameters=GPIO_Label,GPIO_ModeDefaultEXTI
PB6.GPIO_Label=ENCA_L
PB6.GPIO_ModeDefaultEXTI=GPIO_MODE_IT_RISING_FALLING
PB6.Signal=GPXTI6
PB7.GPIOParameters=GPIO_Label
PB7.GPIO_Label=IR_R_IN
PB7.Signal=GPIO_Input
PB8.GPIOParameters=GPIO_Label
PB8.GPIO_Label=IR_L_IN
PB8.Signal=GPIO_Input
PB9.GPIOParameters=GPIO_Speed,GPIO_Label
PB9.GPIO_Label=S0_mux
PB9.GPIO_Speed=GPIO_SPEED_FREQ_HIGH
PB9.Signal=GPIO_Output
PC13-TAMPER-RTC.GPIOParameters=GPIO_Speed,GPIO_Label
PC13-TAMPER-RTC.GPIO_Label=S1_mux
PC13-TAMPER-RTC.GPIO_Speed=GPIO_SPEED_FREQ_HIGH
PC13-TAMPER-RTC.Signal=GPIO_Output
PC14-OSC32_IN.GPIOParameters=GPIO_Speed,GPIO_Label
PC14-OSC32_IN.GPIO_Label=S2_mux
PC14-OSC32_IN.GPIO_Speed=GPIO_SPEED_FREQ_HIGH
PC14-OSC32_IN.Signal=GPIO_Output
PC15-OSC32_OUT.GPIOParameters=GPIO_Speed,GPIO_Label
PC15-OSC32_OUT.GPIO_Label=S3_mux
PC15-OSC32_OUT.GPIO_Speed=GPIO_SPEED_FREQ_HIGH
PC15-OSC32_OUT.Signal=GPIO_Output
PD0-OSC_IN.Mode=HSE-External-Oscillator
PD0-OSC_IN.Signal=RCC_OSC_IN
PD1-OSC_OUT.Mode=HSE-External-Oscillator
PD1-OSC_OUT.Signal=RCC_OSC_OUT
RCC.SYSCLKFreq_VALUE=72000000
RCC.SYSCLKSource=RCC_SYSCLKSOURCE_PLLCLK
board=custom

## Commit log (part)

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2026-03-26 Proyecto unido Hardware y Software
2026-03-26 Corregido submodulo creado
2026-03-26 Ahora deberia incluir la carpeta de stm32
2026-04-10 mejora de lectura de sensores
2026-04-10 eliminando carpeta history
2026-04-10 velocidad a 300 por probar en pista grande
2026-05-02 Se mejoro el MPU6500 por errores
2026-05-03 Codigo corregido y eliminado varias funciones revisar menu para ver si quitar cosas
2026-05-04 Corregido PID y funcionando, borrar demas logica de encoders para no generar problemas de mando
2026-05-07 probado pid
